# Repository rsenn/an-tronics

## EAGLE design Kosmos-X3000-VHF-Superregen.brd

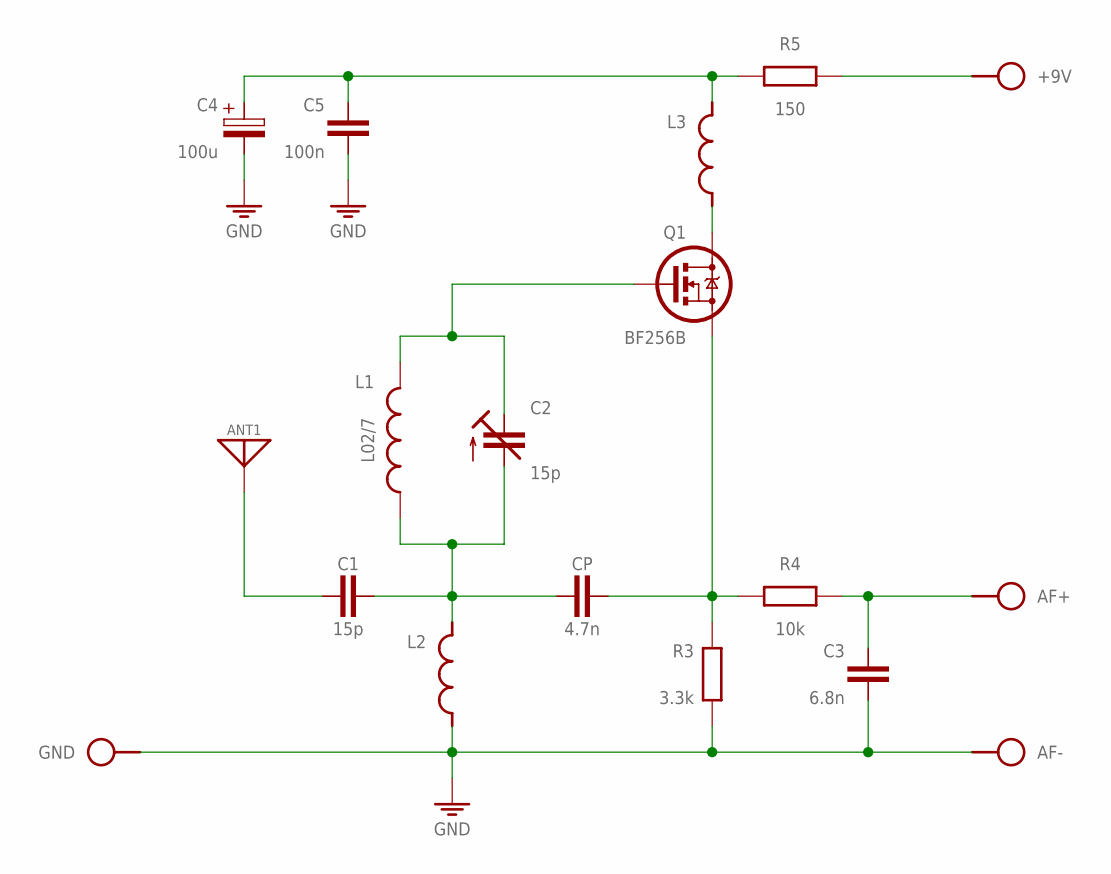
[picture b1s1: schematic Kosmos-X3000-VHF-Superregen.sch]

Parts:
+9V: SPAD
AF+: SPAD
AF-: SPAD
ANT1: ANT; SPAD
C1: 15p; C025-015X024
C2: 15p; TRIM-2222-808
C3: 6.8n; C050-020X044
C4: 100u; E2.5-4/V
C5: 100n; C025-015X024
CP: 4.7n; C025-015X024
GND: SPAD
L1: L02/7; L-02/7V
L2: L-SHORT02/5; L-02/5V
L3: L-SHORT02/7V; L-02/7V
Q1: BF256B; TO92
R3: 3.3k; 0204/10
R4: 10k; 0204/10
R5: 150; 0204/10

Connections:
GND: AF-.1, C3.2, C4.-, C5.2, GND.1, L2.2, R3.1
unnamed: CP.1, Q1.2 (S), R3.2, R4.1
unnamed: AF+.1, C3.1, R4.2
unnamed: ANT1.1, C1.2
unnamed: C4.+, C5.1, L3.1, R5.1
unnamed: C2.3 (E), L1.2, Q1.1 (G)
unnamed: C1.1, C2.2 (A), CP.2, L1.1, L2.1
unnamed: L3.2, Q1.3 (D)
unnamed: +9V.1, R5.2

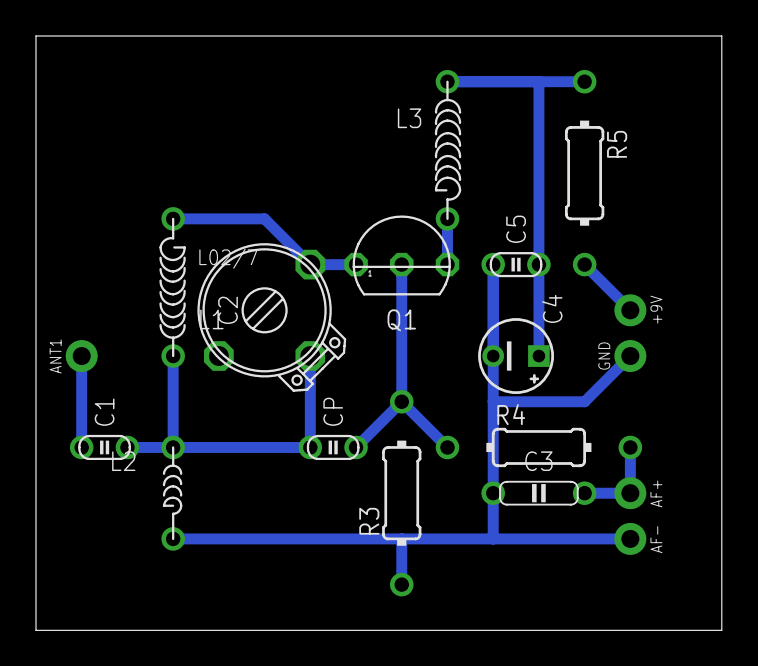
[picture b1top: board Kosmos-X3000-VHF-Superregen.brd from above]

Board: 2 copper layers, 38.1 x 33.0 mm, 18 parts (0 on the bottom side), 9 nets.

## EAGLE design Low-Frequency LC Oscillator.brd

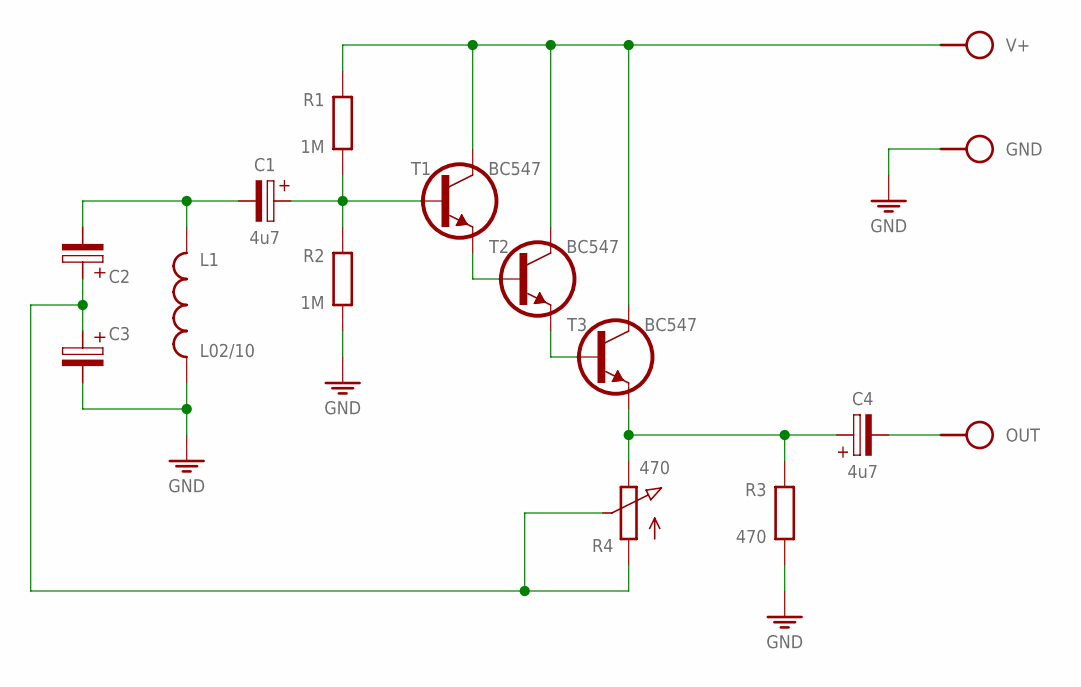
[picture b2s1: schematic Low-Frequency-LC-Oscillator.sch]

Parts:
C1, C4: 4u7; E2,5-3
C2, C3: CPOLE2.5-5; E2,5-5
GND: SPAD
L1: L02/10; L-03/10V
OUT: SPAD
R1, R2: 1M; 0204/10
R3: 470; 0204/10
R4: 470; POT
T1, T2, T3: BC547; TO92-CBE
V+: SPAD

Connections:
GND: C3.-, GND.1, L1.2, R2.1, R3.1
unnamed: R1.2, T1.C, T2.C, T3.C, V+.1
unnamed: C4.-, OUT.1
unnamed: C4.+, R3.2, R4.3 (E), T3.E
unnamed: T1.E, T2.B
unnamed: T2.E, T3.B
unnamed: C1.-, C2.-, L1.1
unnamed: C1.+, R1.1, R2.2, T1.B
unnamed: C2.+, C3.+, R4.1 (A), R4.2 (S)

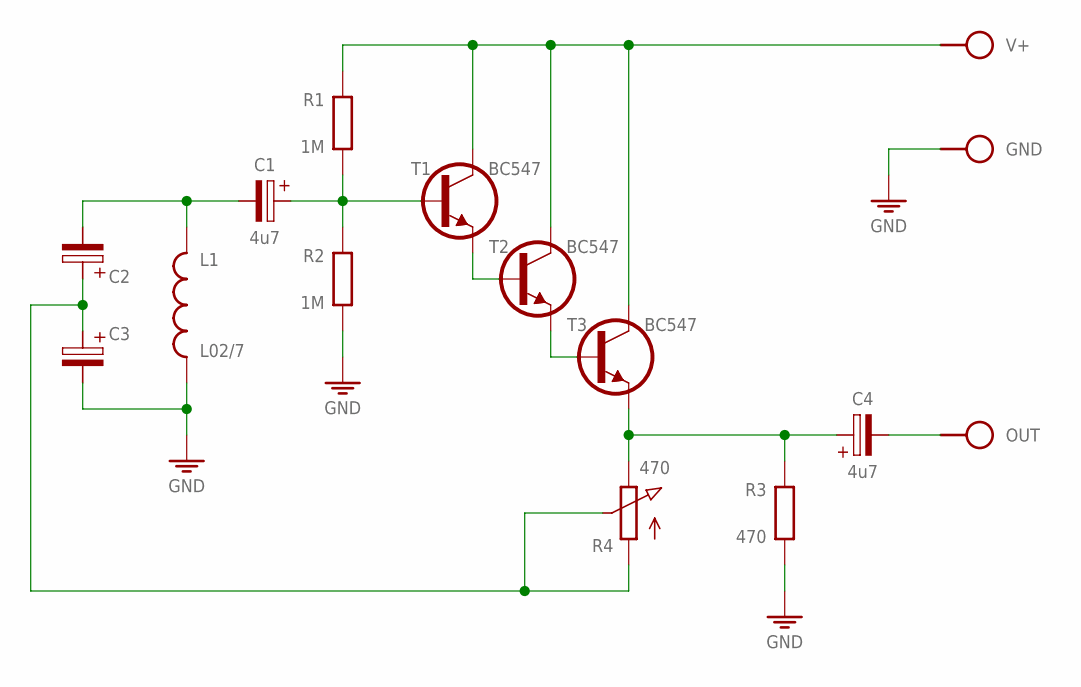
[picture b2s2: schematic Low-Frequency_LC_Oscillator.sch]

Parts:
C1, C4: 4u7; E2,5-3
C2, C3: CPOLE2.5-5; E2,5-5
GND: SPAD
L1: L02/7; L-02/7V
OUT: SPAD
R1, R2: 1M; 0204/10
R3: 470; 0204/10
R4: 470; POT
T1, T2, T3: BC547; TO92-CBE
V+: SPAD

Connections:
GND: C3.-, GND.1, L1.2, R2.1, R3.1
unnamed: R1.2, T1.C, T2.C, T3.C, V+.1
unnamed: C4.-, OUT.1
unnamed: C4.+, R3.2, R4.3 (E), T3.E
unnamed: T1.E, T2.B
unnamed: T2.E, T3.B
unnamed: C1.-, C2.-, L1.1
unnamed: C1.+, R1.1, R2.2, T1.B
unnamed: C2.+, C3.+, R4.1 (A), R4.2 (S)

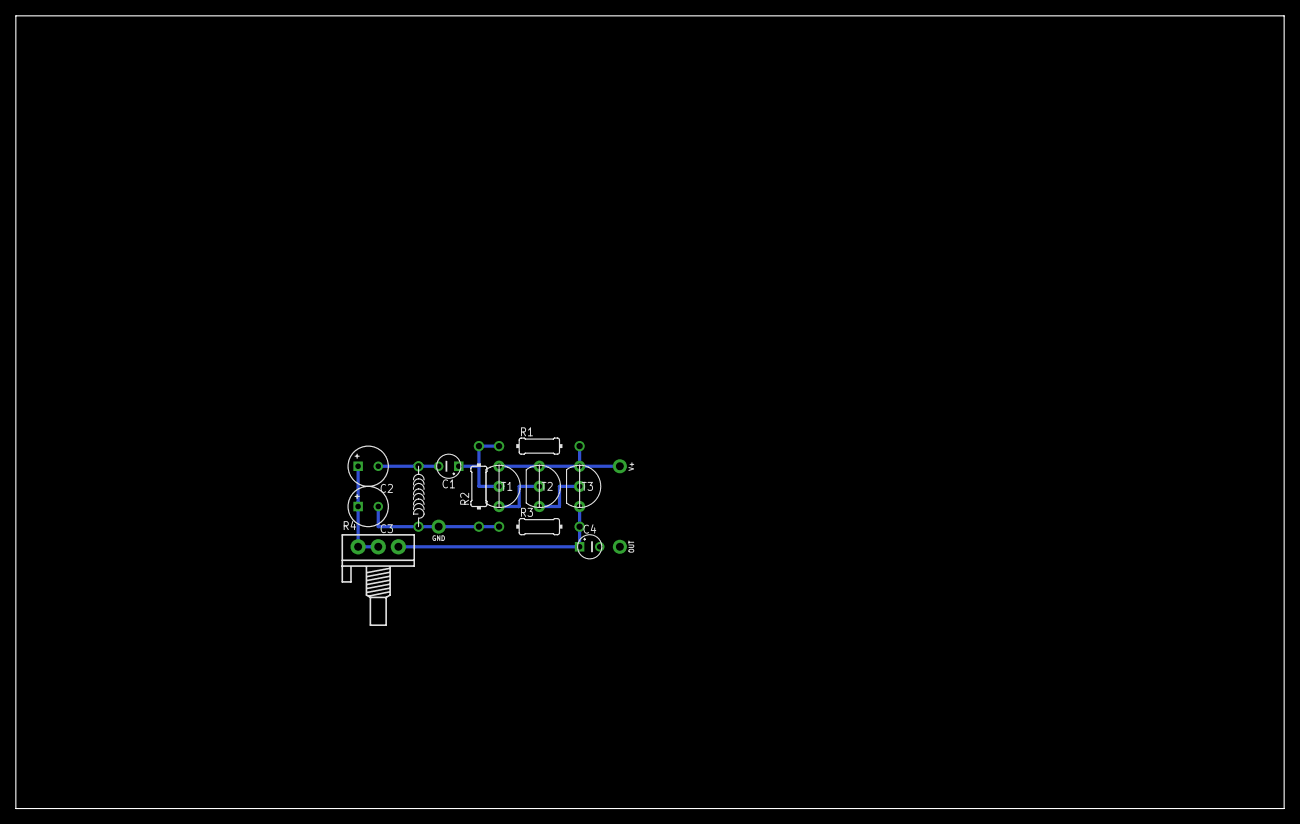
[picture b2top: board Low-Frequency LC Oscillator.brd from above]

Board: 2 copper layers, 160.0 x 100.0 mm, 15 parts (0 on the bottom side), 9 nets.

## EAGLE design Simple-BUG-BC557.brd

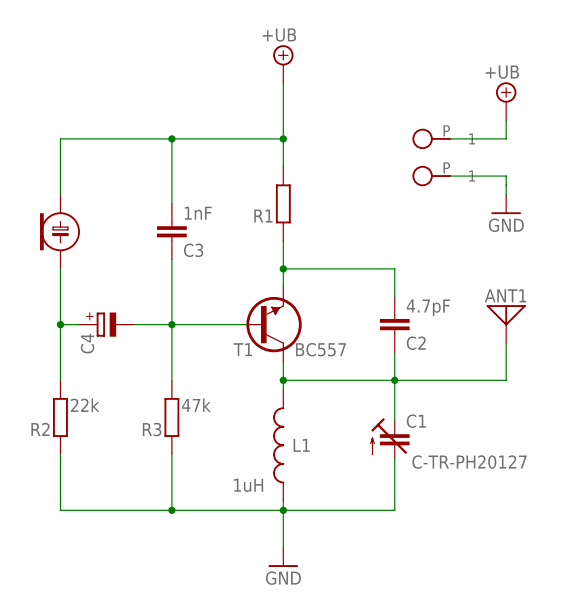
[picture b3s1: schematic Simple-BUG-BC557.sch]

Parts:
+: SPAD
ANT1: ANT; SPAD
C1: C-TR-PH20127; TRIM808-45
C2: 4.7pF; C050-020X036
C3: 1nF; C050-020X036
C4: CPOLE2,5-3; E2,5-3
ECM: ECM-5
L1: 1uH; L-04/7
R1: R0202V; 0202V
R2: 22k; 0202/5
R3: 47k; 0202/5
T1: BC557; TO92-CBE-A
̶̶: SPAD

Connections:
+UB: +.P, C3.2, ECM.1 (+), R1.1
GND: C1.2 (A), L1.2, R2.2, R3.2, ̶̶.P
unnamed: ANT1.P, C1.3 (E), C2.1, L1.1, T1.C
unnamed: C2.2, R1.2, T1.E
unnamed: C3.1, C4.-, R3.1, T1.B
unnamed: C4.+, ECM.2 (-), R2.1

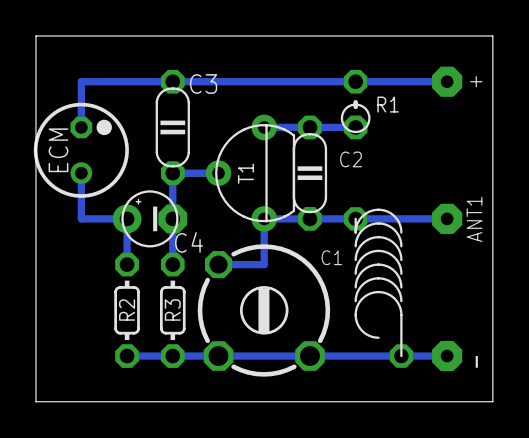
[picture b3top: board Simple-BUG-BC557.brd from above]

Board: 2 copper layers, 25.4 x 20.3 mm, 13 parts (0 on the bottom side), 6 nets.

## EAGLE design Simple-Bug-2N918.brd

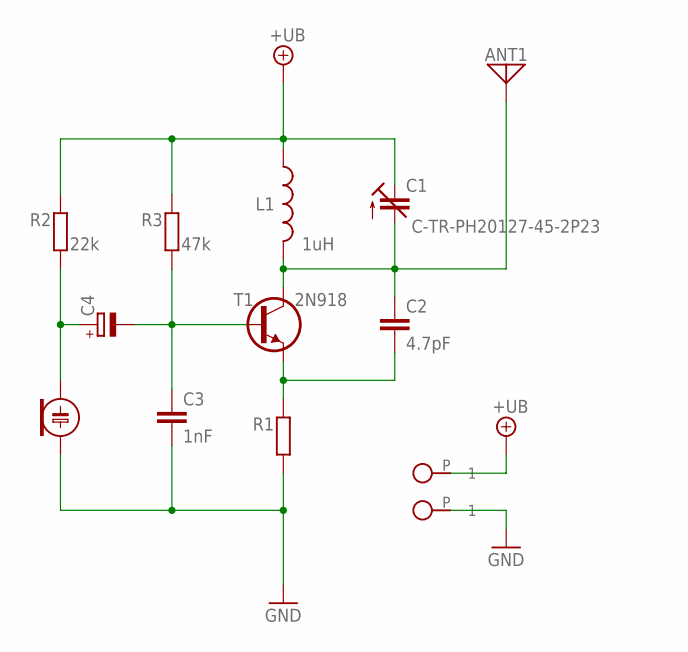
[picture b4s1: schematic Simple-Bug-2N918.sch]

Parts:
+: SPAD
ANT1: ANT; SPAD
C1: C-TR-PH20127-45-2P23; TRIM808-45
C2: 4.7pF; C025-020X036
C3: 1nF; C025-020X036
C4: CPOLE2,5-3; E2,5-3
ECM: ECM-5
L1: 1uH; L-04/7
R1: R0202V; 0202V
R2: 22k; 0202/5
R3: 47k; 0202/5
T1: 2N918; TO-72-A45
̶̶: SPAD

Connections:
+UB: +.P, C1.3 (E), L1.1, R2.2, R3.2
GND: C3.2, ECM.1 (+), R1.1, ̶̶.P
unnamed: ANT1.P, C1.2 (A), C2.1, L1.2, T1.3 (C)
unnamed: C2.2, R1.2, T1.1 (E)
unnamed: C3.1, C4.-, R3.1, T1.2 (B)
unnamed: C4.+, ECM.2 (-), R2.1

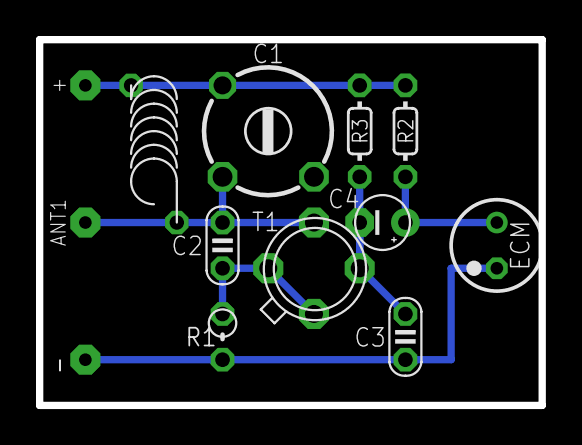
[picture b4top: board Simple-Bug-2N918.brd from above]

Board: 2 copper layers, 27.9 x 20.3 mm, 13 parts (0 on the bottom side), 6 nets.

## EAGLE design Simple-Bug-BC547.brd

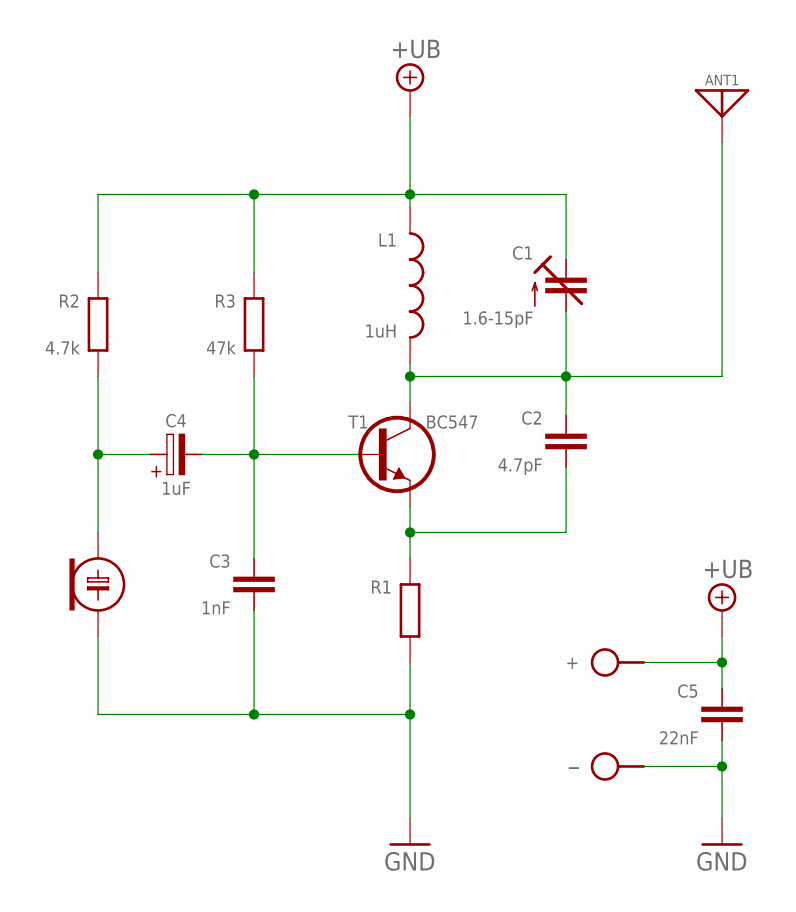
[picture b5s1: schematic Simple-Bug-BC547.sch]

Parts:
+: SPAD
ANT1: ANT; SPAD
C1: 1.6-15pF; TRIM-2222-808
C2: 4.7pF; C050-020X036
C3: 1nF; C050-020X036/V
C4: 1uF; E2,5-3
C5: 22nF; C050-020X036
ECM: ECM-4
L1: 1uH; L-04/7V
R1: R0202/5; 0202/5
R2: 4.7k; 0202/5
R3: 47k; 0202/5
T1: BC547; TO92-CBE-A
̶̶: SPAD

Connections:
+UB: +.1, C1.1 (E), C1.3 (E), C5.1, L1.1, R2.2, R3.2
GND: C3.2, C5.2, ECM.2 (-), R1.1, ̶̶.1
unnamed: ANT1.1, C1.2 (A), C2.1, L1.2, T1.C
unnamed: C2.2, R1.2, T1.E
unnamed: C3.1, C4.-, R3.1, T1.B
unnamed: C4.+, ECM.1 (+), R2.1

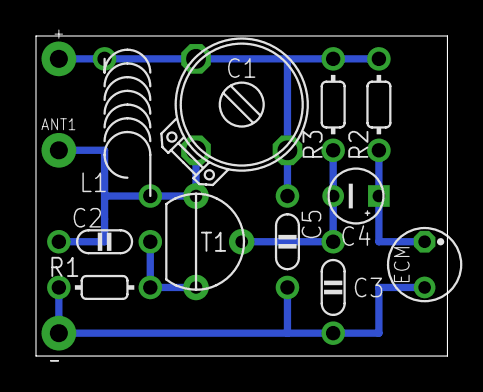
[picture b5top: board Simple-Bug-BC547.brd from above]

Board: 2 copper layers, 22.9 x 17.8 mm, 14 parts (0 on the bottom side), 6 nets.
